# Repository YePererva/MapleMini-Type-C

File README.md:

# Maple Mini (Type C)

[Work In Progress]

This repository contains my modification of STM32F103-based development board, widely known as [Maple Mini](https://www.leaflabs.com/maple/).

Originally, [Maple Mini](https://github.com/leaflabs/maplemini) was developed by [LeafLabs](https://www.leaflabs.com/) and was later modified by some third-party developer and sold under [Baite](https://stm32duinoforum.com/forum/viewtopic_f_38_t_2621.html) brand.

I wanted to introduce the USB type C connector and keep this schematic as example of minimal working infrastructure of STM32F103 microcontrollers for further hobbyist projects.

Here are schematics with added USB type C to both variations of boards.

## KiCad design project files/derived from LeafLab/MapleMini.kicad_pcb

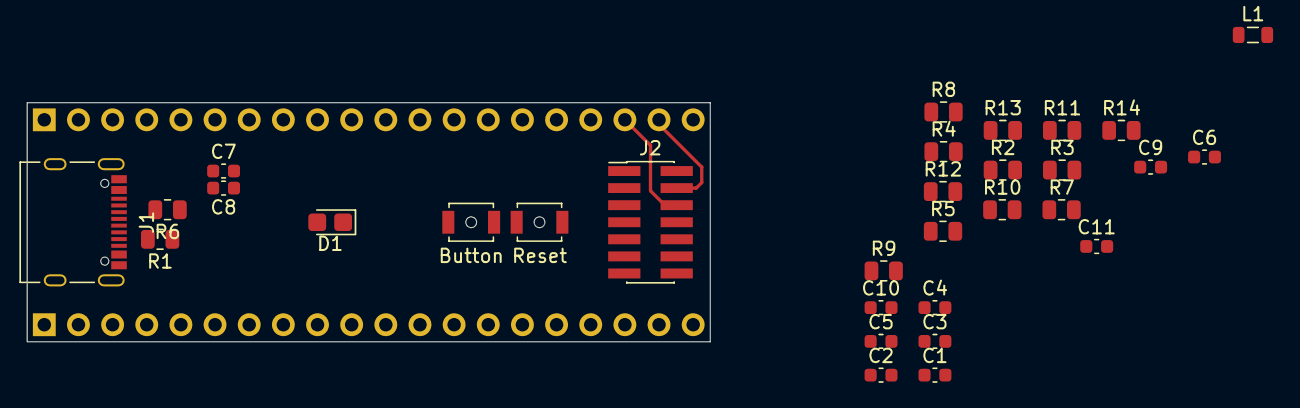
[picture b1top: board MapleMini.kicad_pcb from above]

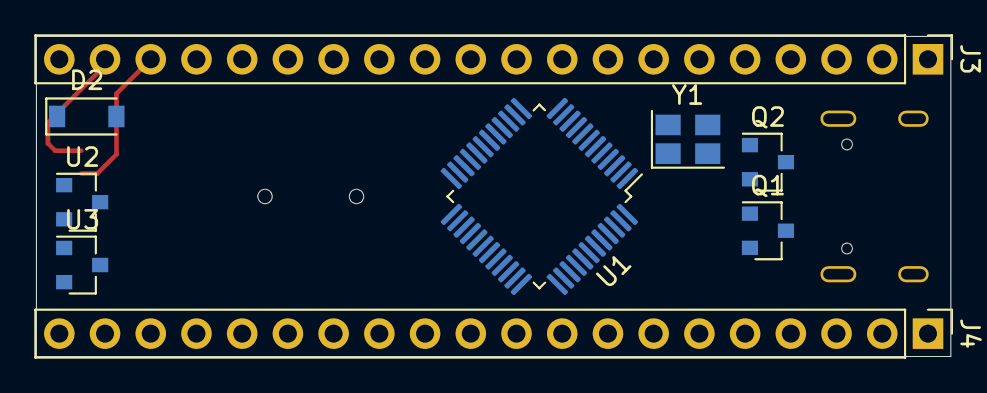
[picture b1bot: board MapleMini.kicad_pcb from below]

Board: 2 copper layers, 50.8 x 17.8 mm, 40 parts (9 on the bottom side), 56 nets.

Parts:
C1, C2, C3, C4: 100nF; C_0603_1608Metric
C5, C6: 47pF; C_0603_1608Metric
C7, C8: 18pF; C_0603_1608Metric
C9, C11: 10uF; C_0603_1608Metric
C10: 100uF; C_0603_1608Metric
D1: Blue; LED_0805_2012Metric_Castellated
D2: D; D_SOD-123
J1: USB_C; USB_C_Receptacle_Palconn_UTC16-G
J2: Conn_ST_STDC14; PinHeader_2x07_P1.27mm_Vertical_SMD
J3: Left; PinHeader_1x20_P2.54mm_Vertical
J4: Right; PinHeader_1x20_P2.54mm_Vertical
L1: 10uH; L_0805_2012Metric
Q1, Q2: BC817; SOT-23
R1, R12: 1.5K; R_0805_2012Metric
R2, R3: 5.1K; R_0805_2012Metric
R4, R10, R14: 10K; R_0805_2012Metric
R5: 47K; R_0805_2012Metric
R6, R9: 22; R_0805_2012Metric
R7: 36K; R_0805_2012Metric
R8, R11, R13: 1K; R_0805_2012Metric
SW1: Reset; SW_SPST_B3U-1000P-B
SW2: Button; SW_SPST_B3U-1000P-B
U1: STM32F103CBTx; LQFP-48_7x7mm_P0.5mm
U2, U3: MCP1703A-3302_SOT23; SOT-23
Y1: 8MHz; Crystal_SMD_SeikoEpson_TSX3225-4Pin_3.2x2.5mm

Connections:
/2: J3.17, U1.20
/3: J3.16, U1.18
/4: J3.15, U1.17
/5: J3.14, U1.16
/6: J3.13, U1.15
/7: J3.12, U1.14
/8: J3.11, U1.13
/9: J3.10, U1.12
/10: J3.9, U1.11
/11: J3.8, U1.10
/12: J3.6, U1.4
/13: J3.4, U1.3
/14: J3.5, U1.2
/15: J4.4, U1.43
/16: J4.5, U1.42
/17: J4.6, U1.41
/18: J4.7, U1.40
/20: J4.9, U1.38
/21: J4.10, U1.37
/22: J4.11, U1.34
/27: J4.16, U1.29
/28: J4.17, U1.28
/29: J4.18, U1.27
/30: J4.19, U1.26
/31: J4.20, U1.25
/33: R12.2, U1.19
/DISC: R8.2, U1.46
BOOT: J4.3, U1.45
BOOT0: R11.2, SW2.2, U1.44
GNDA: C1.2, C11.2, J3.2, L1.1, U1.8
GNDD: C2.2, C3.2, C4.2, C5.2, C6.2, C7.2, C8.2, C9.2, C10.2, D1.1, J1.A1, J1.A12, J1.B1, J1.B12, J1.S1, J2.5, J2.7, J2.11, J4.2, L1.2, Q2.2, R2.1, R3.1, R7.2, R13.2, R14.2, U1.23, U1.35, U1.47, U2.1, U3.1, Y1.2, Y1.4
unnamed: D1.2, R12.1
unnamed: J1.A5, R2.2
unnamed: J1.A6, J1.B6, R9.1
unnamed: J1.A7, J1.B7, R6.2
unnamed: J1.B5, R3.2
unnamed: Q1.1, Q2.3, R4.2, R7.1
unnamed: Q1.2, R1.2
unnamed: Q2.1, R5.2, R8.1
unnamed: R13.1, SW1.1
unnamed: R14.1, SW2.1
OSC_IN: C8.1, U1.5, Y1.3
OSC_OUT: C7.1, U1.6, Y1.1
RESET: J2.12, J3.7, R10.2, SW1.2, U1.7
RX: J2.14, J4.14, U1.31
SWCLK: J2.6, J3.18, U1.21
SWDIO: J2.4, J3.19, U1.22
SWO: J2.8, J4.8, U1.39
TX: J2.13, J4.15, U1.30
USB(+): C5.1, J4.13, R1.1, R9.2, U1.32
USB(-): C6.1, J4.12, R6.1, U1.33
VAA: C1.1, C11.1, J3.1, U1.9, U3.2
VBUS: D2.2, J1.A4, J1.A9, J1.B4, J1.B9, R4.1
VCC: C2.1, C3.1, C4.1, C9.1, J2.3, J4.1, Q1.3, R5.1, R10.1, R11.1, U1.24, U1.36, U1.48, U2.2
Vbat: J3.3, U1.1
Vin: C10.1, D2.1, J3.20, U2.3, U3.3

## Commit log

2020-09-07 Schematics
2020-10-23 Updates after re-oopening in KiCAD 5.1.7
2020-10-23 major re-arrangements
    - Added references
    - Added second schematic as derived from (supposengly) BAITE clone
    - Renamed first design as LeafLabs-derived
    - Added README.md
2020-10-23 Coments on schematics
2020-10-23 Diode search
2020-10-25 Added STDC connectors
2020-10-25 RX/TX mistake fixed
2020-11-05 power nets renaming
2020-11-11 added extra references
